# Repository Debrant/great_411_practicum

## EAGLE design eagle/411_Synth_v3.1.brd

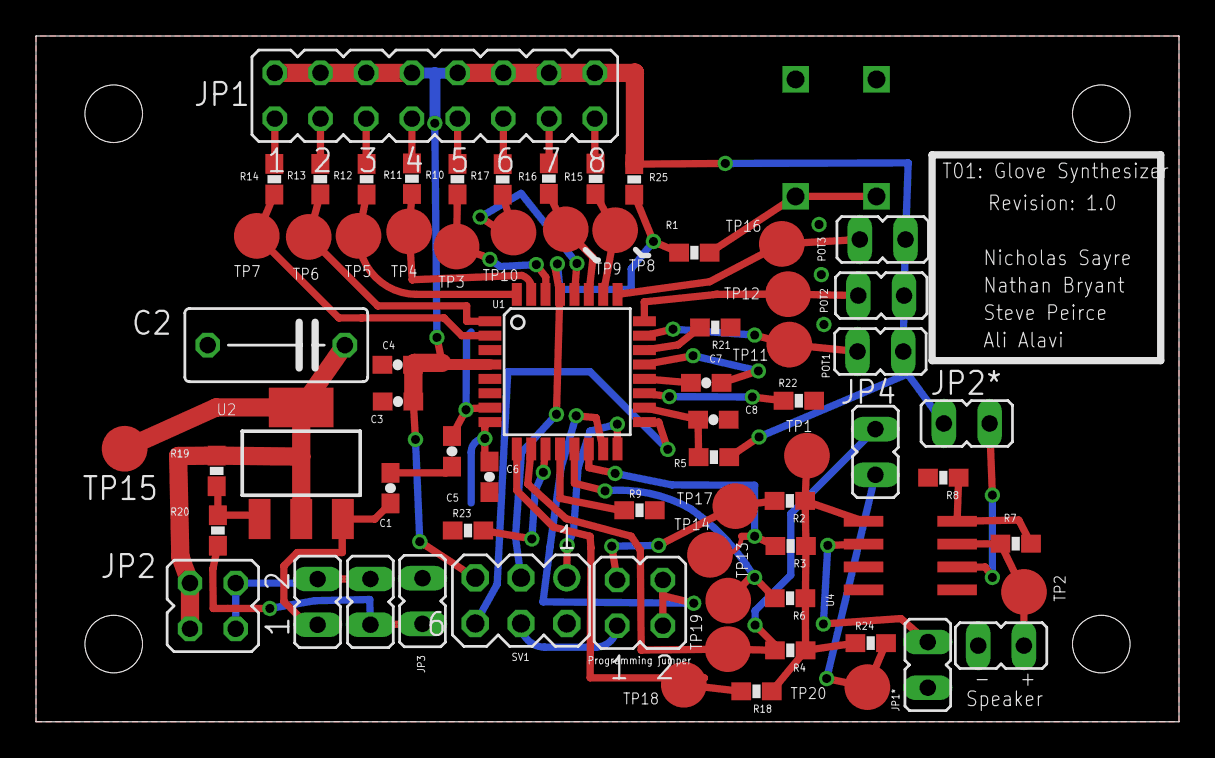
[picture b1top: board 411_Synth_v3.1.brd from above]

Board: 2 copper layers, 63.5 x 38.1 mm, 72 parts (1 on the bottom side), 50 nets.

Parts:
20MHZ: CSM-7X; CSM-7X-DU
C1: 10u; 0603-CAP
C2: 100u; C075-042X103
C3, C4, C7, C8: 100n; 0603-CAP
C5, C6: 22p; 0603-CAP
JP1: 0; JP8Q
JP1*, JP2*, JP3, JP4: 0; JP1
JP2: 0; JP2Q
POT1, POT2, POT3: 0; JP1
PROG.JMP: 0; JP2Q
R1, R20: 330; 0603-RES
R2, R3, R5, R6, R8, R18: 100k; 0603-RES
R4, R24: NP; 0603-RES
R7, R9, R10, R11, R12, R13, R14, R15, R16, R17, R21, R22, R23: 1k; 0603-RES
R19: 100; 0603-RES
R25: 10k; 0603-RES
SV1: 0; MA03-2
SW1: RESET_BUTTON
TP1, TP2, TP3, TP4, TP5, TP6, TP7, TP8, TP9, TP10, TP11, TP12, TP13, TP14, TP15, TP16, TP17, TP18, TP19, TP20: PTR1B2,54; B2,54
U1: ATMEGA328P; TQFP32-08
U2: ZLDO1117; SOT223
U4: LT1013; SO08
U$1: SPEAKER; JP1
U$7: POWER_SWITCH; JP1
U$8: 9VOLTBATTERY; JP1

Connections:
5V: C2.1, JP2.3, JP2.4, R19.2, TP15.TP, U2.2, U2.4
9V: JP2.1, JP2.2, U$7.1, U$8.1
+5V: C3.1, C4.1, JP1.2, JP1.4, JP1.6, JP1.8, JP1.10, JP1.12, JP1.14, JP1.16, JP2*.2, POT1.1, POT2.1, POT3.1, R5.2, R25.2, SV1.5, U1.4
GND: C1.2, C2.2, C3.2, C4.2, C5.2, C6.2, C7.2, C8.2, JP1*.2, JP3.1, JP3.2, R8.2, R9.1, R20.1, R21.1, R22.1, R23.1, SV1.2, SW1.1, SW1.2, U1.3, U1.5, U1.21, U4.3, U4.4, U4.5, U$1.2, U$8.2
MISO: SV1.1, U1.16
MOSI: PROG.JMP.1, SV1.4
unnamed: C7.1, U1.20
unnamed: R2.1, R3.1, R4.1, R6.1, R18.1, R24.1, TP1.TP, U4.1
unnamed: JP1.9, R10.2
unnamed: JP1.7, R11.2
unnamed: JP1.5, R12.2
unnamed: 20MHZ.1, C5.1, U1.7
unnamed: 20MHZ.2, C6.1, U1.8
unnamed: C8.1, R5.1, U1.18
unnamed: R21.2, U1.22
unnamed: R22.2, U1.19
unnamed: JP1.3, R13.2
unnamed: JP1.1, R14.2
unnamed: JP1.15, R15.2
unnamed: JP1.13, R16.2
unnamed: R7.1, R8.1, U4.8
unnamed: R9.2, U1.12
unnamed: JP4.1, R24.2, TP20.TP
unnamed: R1.2, SW1.3, SW1.4
unnamed: JP1.11, R17.2
unnamed: R7.2, TP2.TP, U4.7, U$1.1
unnamed: R19.1, R20.2, U2.1
unnamed: C1.1, U2.3, U$7.2
PB1: R6.2, TP13.TP, U1.13
PB2: R3.2, TP14.TP, U1.14
PB3: PROG.JMP.3, R2.2, TP17.TP
PB3/MOSI: PROG.JMP.2, PROG.JMP.4, U1.15
PC0: POT1.2, TP11.TP, U1.23
PC1: POT2.2, TP12.TP, U1.24
PC2: POT3.2, TP16.TP, U1.25
PC3: R15.1, TP8.TP, U1.26
PC4: R16.1, TP9.TP, U1.27
PC5: R17.1, TP10.TP, U1.28
PD0: R10.1, TP3.TP, U1.30
PD1: R11.1, TP4.TP, U1.31
PD2: R12.1, TP5.TP, U1.32
PD3: R13.1, TP6.TP, U1.1
PD4: R14.1, TP7.TP, U1.2
PD5: R18.2, TP18.TP, U1.9
PD6: JP4.2, R4.2, TP19.TP, U1.10
PD7: R23.2, U1.11
RESET: R1.1, R25.1, SV1.3, U1.29
SCK: SV1.6, U1.17
V+: JP2*.1, U4.6
V-: JP1*.1, U4.2

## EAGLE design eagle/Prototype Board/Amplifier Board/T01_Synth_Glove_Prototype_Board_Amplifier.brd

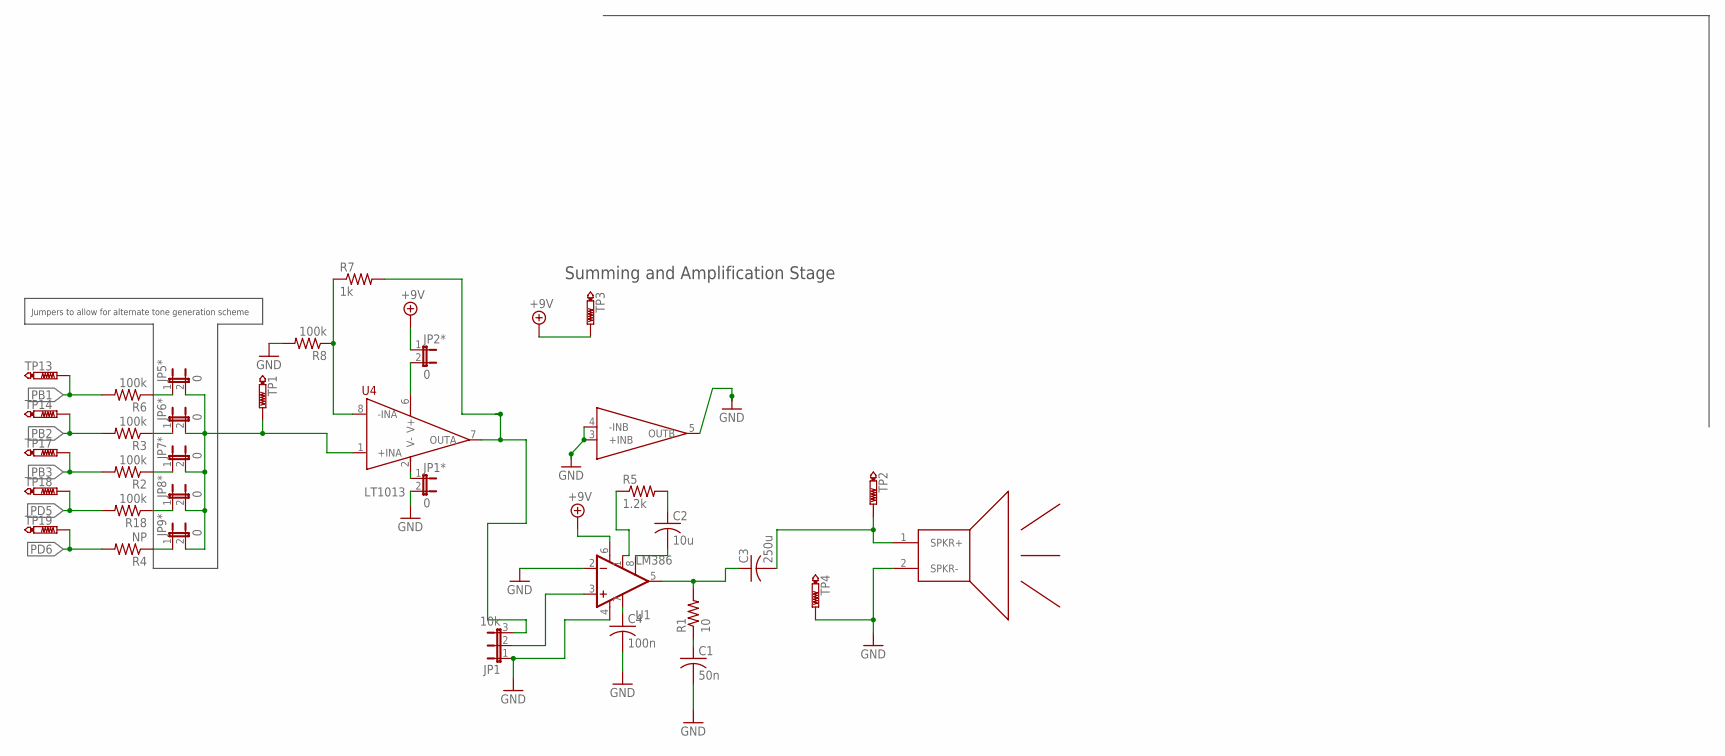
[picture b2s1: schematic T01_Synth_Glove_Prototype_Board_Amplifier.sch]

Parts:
C1: 50n; C025-030X050
C2: 10u; C025-030X050
C3: 250u; C025-030X050
C4: 100n; C025-030X050
JP1: 10k; JP2
JP1*, JP2*, JP5*, JP6*, JP7*, JP8*, JP9*: 0; JP1
R1: 10; 0204V
R2, R3, R6, R8, R18: 100k; 0603-RES
R4: NP; 0603-RES
R5: 1.2k; 0204V
R7: 1k; 0603-RES
TP1, TP2, TP3, TP4, TP13, TP14, TP17, TP18, TP19: PTR1B2,54; B2,54
U1: LM386; DIP08
U4: LT1013; SO08
U$1: SPEAKER; JP1

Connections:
+9V: JP2*.1, TP3.TP, U1.6 (V+)
GND: C1.2, C4.2, JP1.1, JP1*.2, R8.2, TP4.TP, U1.2 (-IN), U1.4 (V-), U4.3 (+INB), U4.4 (-INB), U4.5 (OUTB), U$1.2 (SPKR-)
unnamed: C3.1, R1.2, U1.5 (OUT)
unnamed: JP5*.2, JP6*.2, JP7*.2, JP8*.2, JP9*.2, TP1.TP, U4.1 (+INA)
unnamed: JP1.3, R7.2, U4.7 (OUTA)
unnamed: C1.1, R1.1
unnamed: C3.2, TP2.TP, U$1.1 (SPKR+)
unnamed: C2.2, U1.8 (GAIN)
unnamed: C2.1, R5.2
unnamed: R5.1, U1.1 (GAIN)
unnamed: C4.1, U1.7 (BP)
unnamed: JP1.2, U1.3 (+IN)
unnamed: R7.1, R8.1, U4.8 (-INA)
unnamed: JP5*.1, R6.1
unnamed: JP6*.1, R3.1
unnamed: JP7*.1, R2.1
unnamed: JP2*.2, U4.6 (V+)
unnamed: JP8*.1, R18.1
unnamed: JP9*.1, R4.1
PB1: R6.2, TP13.TP
PB2: R3.2, TP14.TP
PB3: R2.2, TP17.TP
PD5: R18.2, TP18.TP
PD6: R4.2, TP19.TP
V-: JP1*.1, U4.2 (V-)

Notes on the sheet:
Summing and Amplification Stage
Jumpers to allow for alternate tone generation scheme

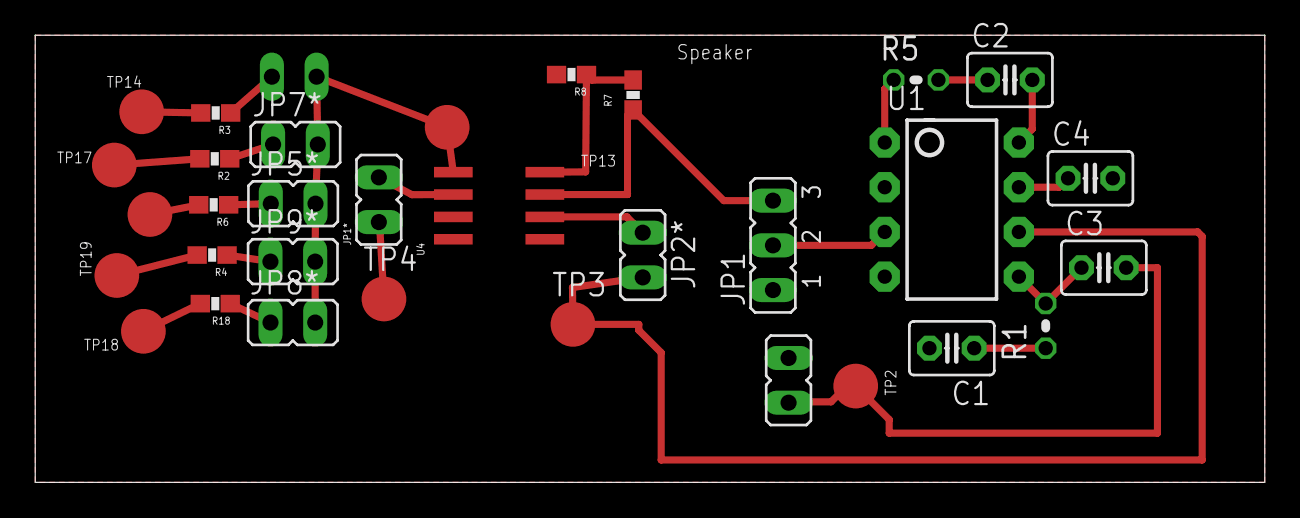
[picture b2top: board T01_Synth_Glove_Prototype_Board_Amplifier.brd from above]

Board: 2 copper layers, 69.8 x 25.4 mm, 33 parts (1 on the bottom side), 25 nets.

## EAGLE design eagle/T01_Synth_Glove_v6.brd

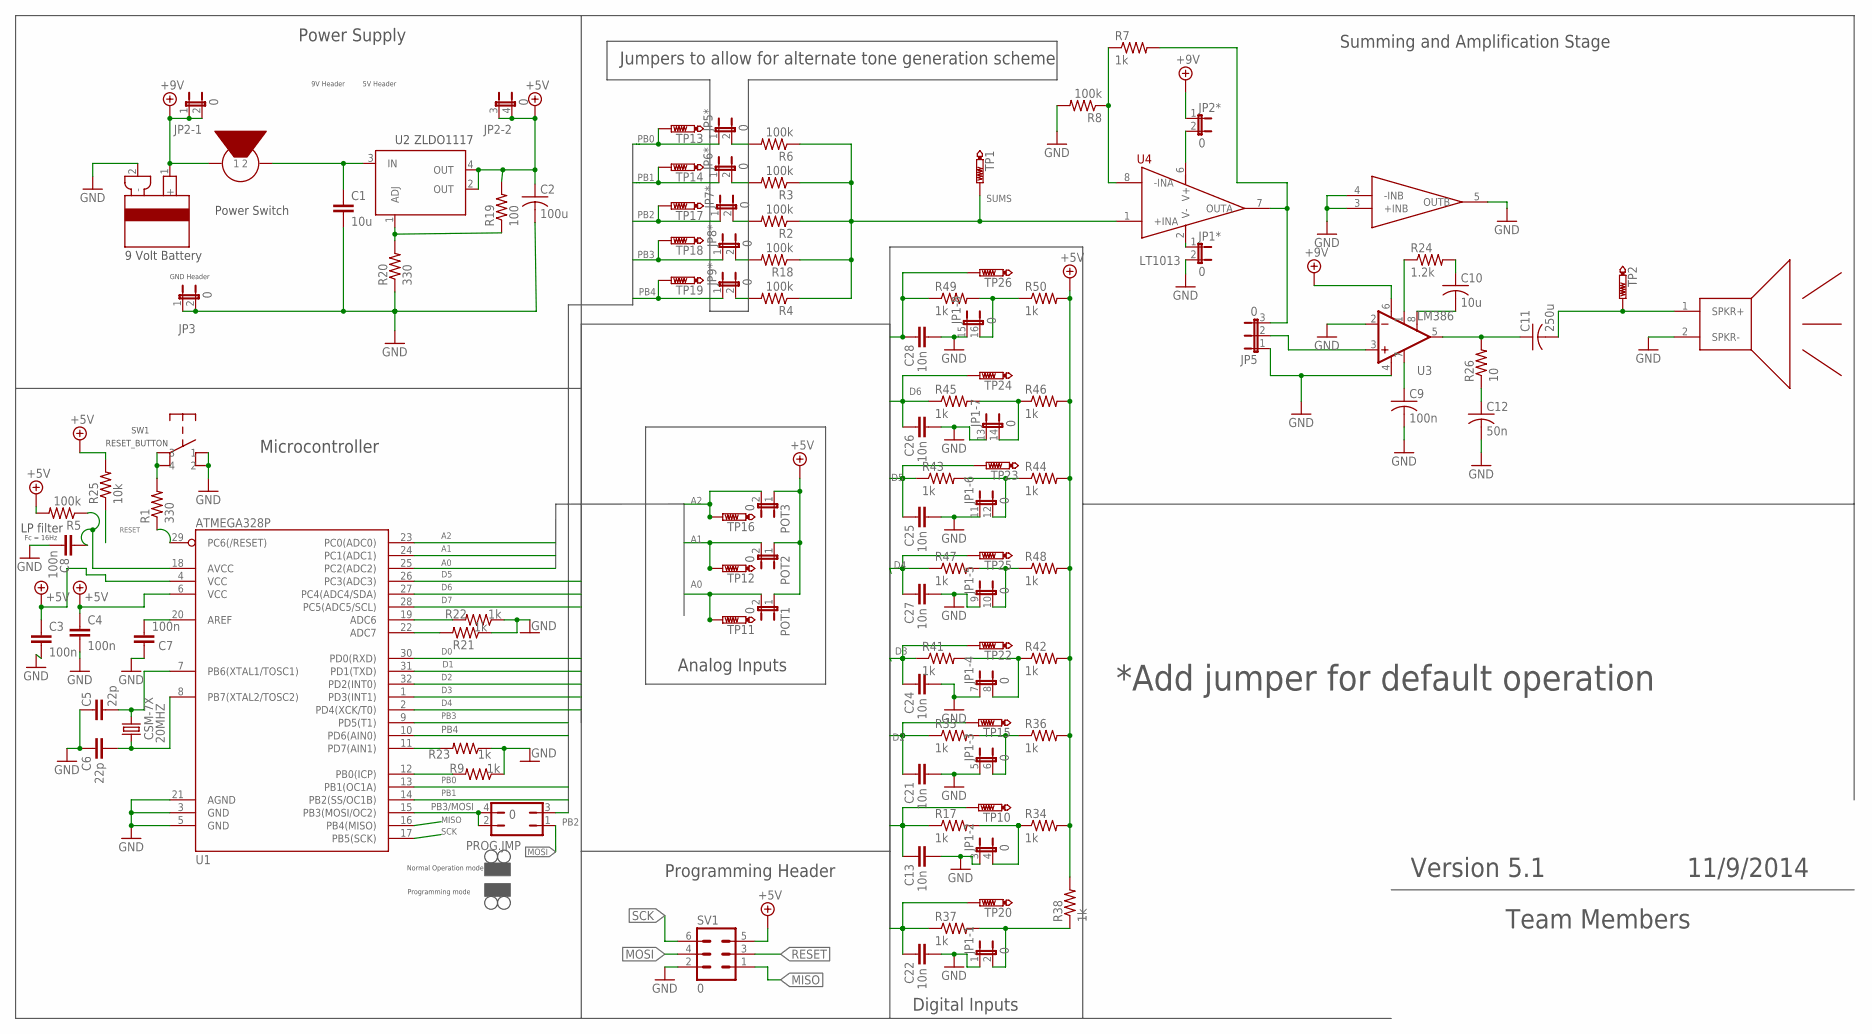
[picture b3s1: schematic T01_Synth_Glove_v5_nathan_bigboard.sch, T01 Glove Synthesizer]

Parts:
20MHZ: CSM-7X; CSM-7X-DU
C1: 10u; 0603-CAP
C2: 100u; C075-042X103
C3, C4, C7, C8: 100n; 0603-CAP
C5, C6: 22p; 0603-CAP
C9: 100n; C025-030X050
C10: 10u; C025-030X050
C11: 250u; C025-030X050
C12: 50n; C025-030X050
C13, C21, C22, C24, C25, C26, C27, C28: 10n; 0603-CAP
JP1: 0; JP8Q
JP1*, JP2*, JP3, JP5*, JP6*, JP7*, JP8*, JP9*: 0; JP1
JP2: 0; JP2Q
JP5: 0; JP2
POT1, POT2, POT3: 0; JP1
PROG.JMP: 0; JP2Q
R1, R20: 330; 0603-RES
R2, R3, R4, R5, R6, R8, R18: 100k; 0603-RES
R7, R9, R17, R21, R22, R23, R34, R35, R36, R37, R38, R41, R42, R43, R44, R45, R46, R47, R48, R49, R50: 1k; 0603-RES
R19: 100; 0603-RES
R24: 1.2k; 0204V
R25: 10k; 0603-RES
R26: 10; 0204V
SV1: 0; MA03-2
SW1: RESET_BUTTON
TP1, TP2, TP10, TP11, TP12, TP13, TP14, TP15, TP16, TP17, TP18, TP19, TP20, TP22, TP23, TP24, TP25, TP26: PTR1B2,54; B2,54
U1: ATMEGA328P; TQFP32-08
U2: ZLDO1117; SOT223
U3: LM386; DIP08
U4: LT1013; SO08
U$1: SPEAKER; JP1
U$7: POWER_SWITCH; JP1
U$8: 9VOLTBATTERY; JP1

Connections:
+5V: C2.1, C3.1, C4.1, JP2.3 (1), JP2.4 (2), POT1.1, POT2.1, POT3.1, R5.2, R19.2, R25.2, R34.2, R36.2, R38.2, R42.2, R44.2, R46.2, R48.2, R50.2, SV1.5, U1.4 (VCC), U1.6 (VCC), U2.2 (OUT), U2.4 (OUT); also elsewhere on the board
+9V: JP2.1, JP2.2, JP2*.1, U3.6 (V+), U$7.1, U$8.1 (+); also elsewhere on the board
A0: POT1.2, TP11.TP, U1.25 (PC2(ADC2))
A1: POT2.2, TP12.TP, U1.24 (PC1(ADC1))
A2: POT3.2, TP16.TP, U1.23 (PC0(ADC0))
D0: C22.2, R37.1, TP20.TP, U1.30 (PD0(RXD))
D1: C13.2, R17.1, TP10.TP, U1.31 (PD1(TXD))
D2: C21.2, R35.1, TP15.TP, U1.32 (PD2(INT0))
D3: C24.2, R41.1, TP22.TP, U1.1 (PD3(INT1))
D4: C27.2, R47.1, TP25.TP, U1.2 (PD4(XCK/T0))
D5: C25.2, R43.1, TP23.TP, U1.26 (PC3(ADC3))
D6: C26.2, R45.1, TP24.TP, U1.27 (PC4(ADC4/SDA))
D7: C28.2, R49.1, TP26.TP, U1.28 (PC5(ADC5/SCL))
MISO: SV1.1, U1.16 (PB4(MISO))
MOSI: PROG.JMP.1, SV1.4
unnamed: C7.1, U1.20 (AREF)
unnamed: 20MHZ.1, C5.1, U1.7 (PB6(XTAL1/TOSC1))
unnamed: 20MHZ.2, C6.1, U1.8 (PB7(XTAL2/TOSC2))
unnamed: C8.1, R5.1, U1.18 (AVCC)
unnamed: R21.2, U1.22 (ADC7)
unnamed: R22.2, U1.19 (ADC6)
unnamed: JP1.6 (2), R35.2, R36.1
unnamed: R7.1, R8.1, U4.8 (-INA)
unnamed: R9.2, U1.12 (PB0(ICP))
unnamed: JP5*.2, R6.2
unnamed: JP9*.2, R4.2
unnamed: R1.2, SW1.3, SW1.4
unnamed: JP8*.2, R18.2
unnamed: C11.2, TP2.TP, U$1.1 (SPKR+)
unnamed: JP7*.2, R2.2
unnamed: JP2*.2, U4.6 (V+)
unnamed: R19.1, R20.2, U2.1 (ADJ)
unnamed: C1.1, U2.3 (IN), U$7.2
unnamed: JP6*.2, R3.2
unnamed: C10.2, U3.8 (GAIN)
unnamed: JP1.2, R37.2, R38.1
unnamed: C11.1, R26.2, U3.5 (OUT)
unnamed: C12.1, R26.1
unnamed: JP1.16 (2), R49.2, R50.1
PB0: JP5*.1, TP13.TP, U1.13 (PB1(OC1A))
PB1: JP6*.1, TP14.TP, U1.14 (PB2(SS/OC1B))
PB2: JP7*.1, PROG.JMP.3, TP17.TP
PB3: JP8*.1, TP18.TP, U1.9 (PD5(T1))
PB3/MOSI: PROG.JMP.2, PROG.JMP.4, U1.15 (PB3(MOSI/OC2))
PB4: JP9*.1, TP19.TP, U1.10 (PD6(AIN0))
PD7: R23.2, U1.11 (PD7(AIN1))
SCK: SV1.6, U1.17 (PB5(SCK))
SUMS: R2.1, R3.1, R4.1, R6.1, R18.1, TP1.TP, U4.1 (+INA)
V-: JP1*.1, U4.2 (V-)

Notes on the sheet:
Power Switch
Programming Header
Digital Inputs
Power Supply
Microcontroller
Summing and Amplification Stage
Analog Inputs
LP filter
*Add jumper for default operation
5V Header
9V Header
GND Header
Fc = 16Hz
Jumpers to allow for alternate tone generation scheme
Programming mode
Normal Operation mode
Team Members
Version 5.1
11/9/2014

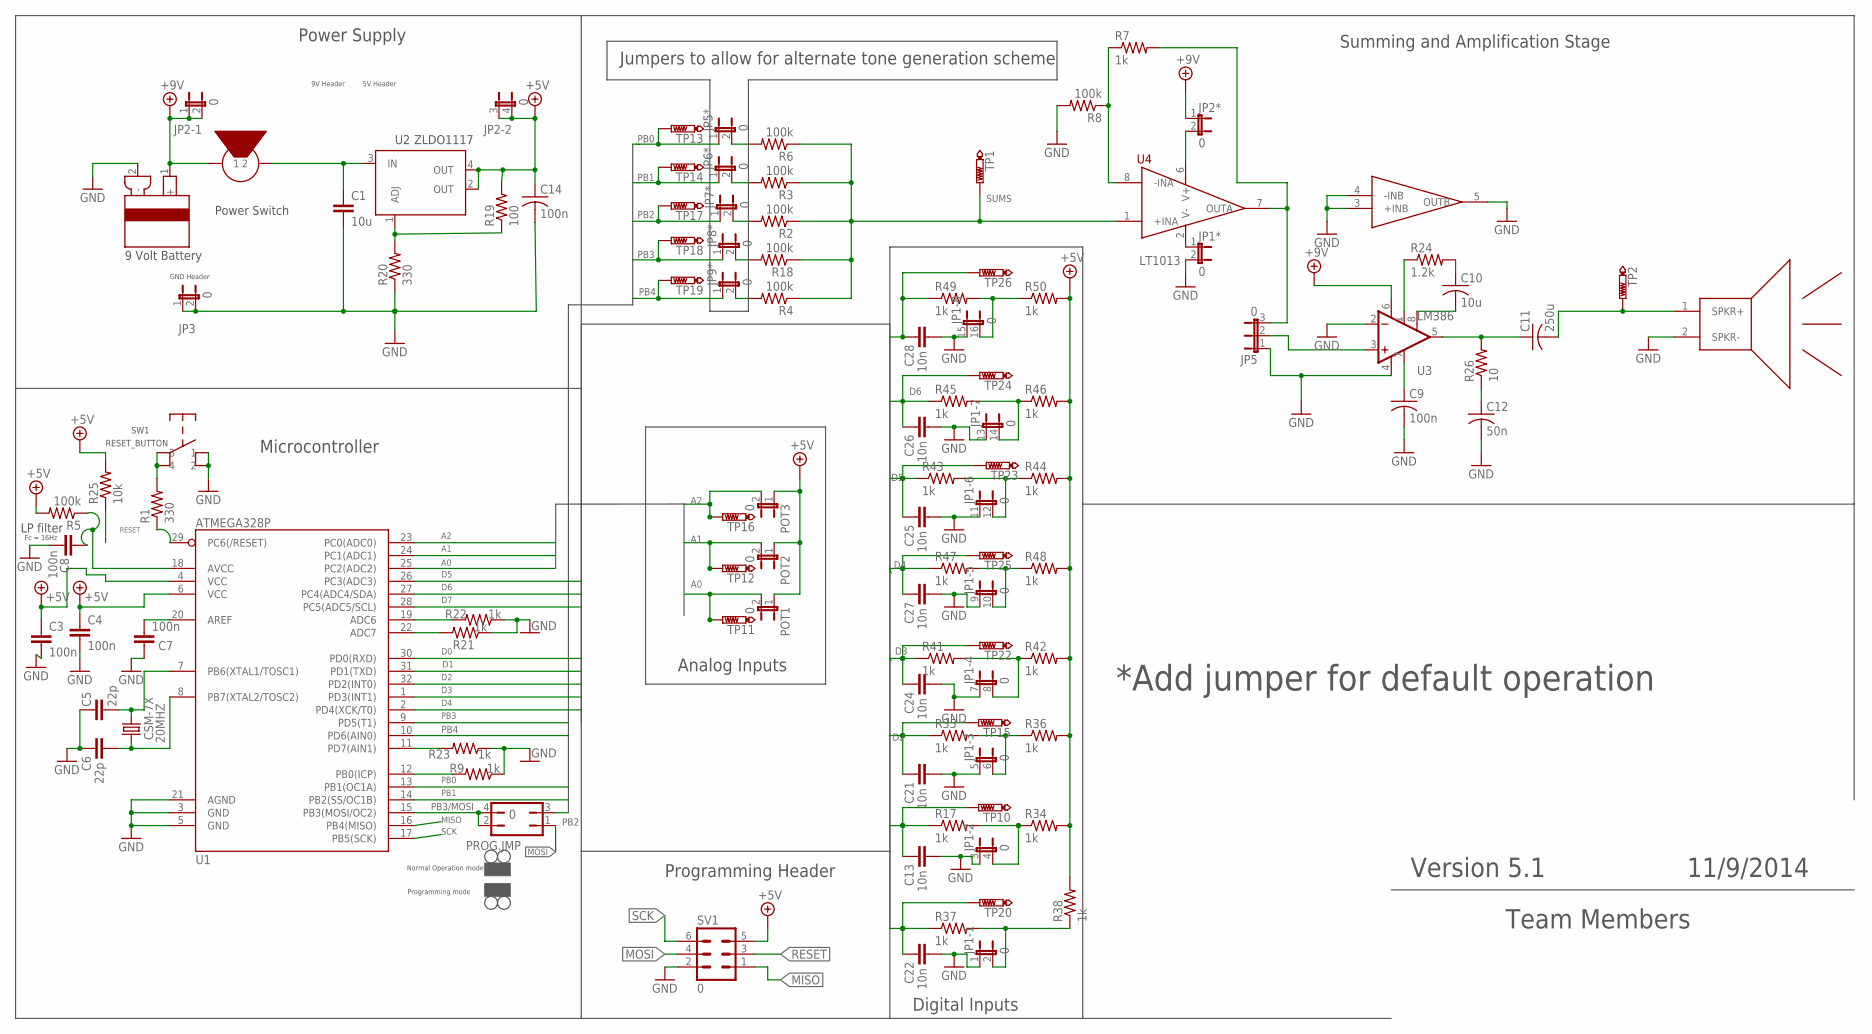
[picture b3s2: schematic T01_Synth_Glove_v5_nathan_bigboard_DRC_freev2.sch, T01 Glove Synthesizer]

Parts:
20MHZ: CSM-7X; CSM-7X-DU
C1: 10u; 0603-CAP
C3, C4, C7, C8: 100n; 0603-CAP
C5, C6: 22p; 0603-CAP
C9, C14: 100n; C025-030X050
C10: 10u; C025-030X050
C11: 250u; C025-030X050
C12: 50n; C025-030X050
C13, C21, C22, C24, C25, C26, C27, C28: 10n; 0603-CAP
JP1: 0; JP8Q
JP1*, JP2*, JP3, JP5*, JP6*, JP7*, JP8*, JP9*: 0; JP1
JP2: 0; JP2Q
JP5: 0; JP2
POT1, POT2, POT3: 0; JP1
PROG.JMP: 0; JP2Q
R1, R20: 330; 0603-RES
R2, R3, R4, R5, R6, R8, R18: 100k; 0603-RES
R7, R9, R17, R21, R22, R23, R34, R35, R36, R37, R38, R41, R42, R43, R44, R45, R46, R47, R48, R49, R50: 1k; 0603-RES
R19: 100; 0603-RES
R24: 1.2k; 0204V
R25: 10k; 0603-RES
R26: 10; 0204V
SV1: 0; MA03-2
SW1: RESET_BUTTON
TP1, TP2, TP10, TP11, TP12, TP13, TP14, TP15, TP16, TP17, TP18, TP19, TP20, TP22, TP23, TP24, TP25, TP26: PTR1B2,54; B2,54
U1: ATMEGA328P; TQFP32-08
U2: ZLDO1117; SOT223
U3: LM386; DIP08
U4: LT1013; SO08
U$1: SPEAKER; JP1
U$7: POWER_SWITCH; JP1
U$8: 9VOLTBATTERY; JP1

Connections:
+5V: C3.1, C4.1, C14.1, JP2.3 (1), JP2.4 (2), POT1.1, POT2.1, POT3.1, R5.2, R19.2, R25.2, R34.2, R36.2, R38.2, R42.2, R44.2, R46.2, R48.2, R50.2, SV1.5, U1.4 (VCC), U1.6 (VCC), U2.2 (OUT), U2.4 (OUT); also elsewhere on the board
+9V: C14.2, JP2.1, JP2.2, JP2*.1, U3.6 (V+), U$7.1, U$8.1 (+)
A0: POT1.2, TP11.TP, U1.25 (PC2(ADC2))
A1: POT2.2, TP12.TP, U1.24 (PC1(ADC1))
A2: POT3.2, TP16.TP, U1.23 (PC0(ADC0))
D0: C22.2, R37.1, TP20.TP, U1.30 (PD0(RXD))
D1: C13.2, R17.1, TP10.TP, U1.31 (PD1(TXD))
D2: C21.2, R35.1, TP15.TP, U1.32 (PD2(INT0))
D3: C24.2, R41.1, TP22.TP, U1.1 (PD3(INT1))
D4: C27.2, R47.1, TP25.TP, U1.2 (PD4(XCK/T0))
D5: C25.2, R43.1, TP23.TP, U1.26 (PC3(ADC3))
D6: C26.2, R45.1, TP24.TP, U1.27 (PC4(ADC4/SDA))
D7: C28.2, R49.1, TP26.TP, U1.28 (PC5(ADC5/SCL))
MISO: SV1.1, U1.16 (PB4(MISO))
MOSI: PROG.JMP.1, SV1.4
unnamed: C7.1, U1.20 (AREF)
unnamed: 20MHZ.1, C5.1, U1.7 (PB6(XTAL1/TOSC1))
unnamed: 20MHZ.2, C6.1, U1.8 (PB7(XTAL2/TOSC2))
unnamed: C8.1, R5.1, U1.18 (AVCC)
unnamed: R21.2, U1.22 (ADC7)
unnamed: R22.2, U1.19 (ADC6)
unnamed: JP1.6 (2), R35.2, R36.1
unnamed: R7.1, R8.1, U4.8 (-INA)
unnamed: R9.2, U1.12 (PB0(ICP))
unnamed: JP5*.2, R6.2
unnamed: JP9*.2, R4.2
unnamed: R1.2, SW1.3, SW1.4
unnamed: JP8*.2, R18.2
unnamed: C11.2, TP2.TP, U$1.1 (SPKR+)
unnamed: JP7*.2, R2.2
unnamed: JP2*.2, U4.6 (V+)
unnamed: R19.1, R20.2, U2.1 (ADJ)
unnamed: C1.1, U2.3 (IN), U$7.2
unnamed: JP6*.2, R3.2
unnamed: C10.2, U3.8 (GAIN)
unnamed: JP1.2, R37.2, R38.1
unnamed: C11.1, R26.2, U3.5 (OUT)
unnamed: C12.1, R26.1
unnamed: JP1.16 (2), R49.2, R50.1
PB0: JP5*.1, TP13.TP, U1.13 (PB1(OC1A))
PB1: JP6*.1, TP14.TP, U1.14 (PB2(SS/OC1B))
PB2: JP7*.1, PROG.JMP.3, TP17.TP
PB3: JP8*.1, TP18.TP, U1.9 (PD5(T1))
PB3/MOSI: PROG.JMP.2, PROG.JMP.4, U1.15 (PB3(MOSI/OC2))
PB4: JP9*.1, TP19.TP, U1.10 (PD6(AIN0))
PD7: R23.2, U1.11 (PD7(AIN1))
SCK: SV1.6, U1.17 (PB5(SCK))
SUMS: R2.1, R3.1, R4.1, R6.1, R18.1, TP1.TP, U4.1 (+INA)
V-: JP1*.1, U4.2 (V-)

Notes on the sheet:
Power Switch
Programming Header
Digital Inputs
Power Supply
Microcontroller
Summing and Amplification Stage
Analog Inputs
LP filter
*Add jumper for default operation
5V Header
9V Header
GND Header
Fc = 16Hz
Jumpers to allow for alternate tone generation scheme
Programming mode
Normal Operation mode
Team Members
Version 5.1
11/9/2014

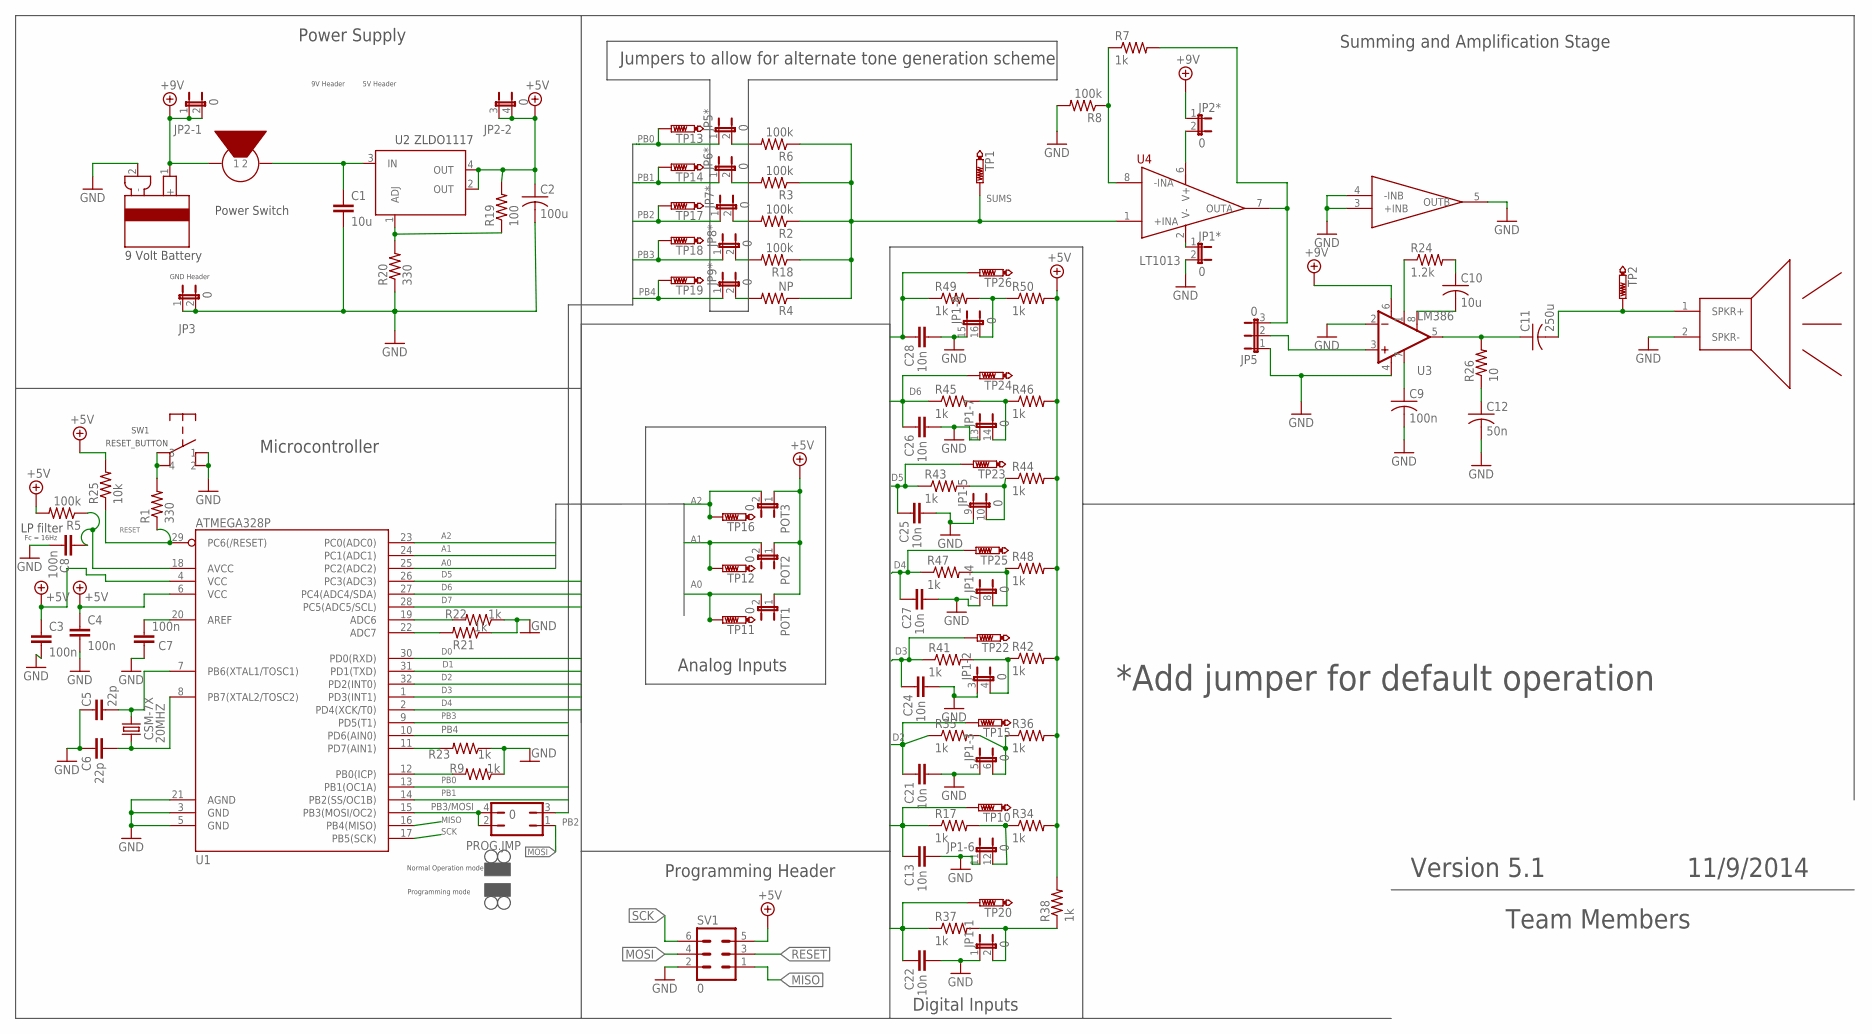
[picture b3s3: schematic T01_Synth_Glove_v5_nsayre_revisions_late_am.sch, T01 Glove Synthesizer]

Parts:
20MHZ: CSM-7X; CSM-7X-DU
C1: 10u; 0603-CAP
C2: 100u; C025-030X050
C3, C4, C7, C8: 100n; 0603-CAP
C5, C6: 22p; 0603-CAP
C9: 100n; C025-030X050
C10: 10u; C025-030X050
C11: 250u; C025-030X050
C12: 50n; C025-030X050
C13, C21, C22, C24, C25, C26, C27, C28: 10n; 0603-CAP
JP1: 0; JP8Q
JP1*, JP2*, JP3, JP5*, JP6*, JP7*, JP8*, JP9*: 0; JP1
JP2: 0; JP2Q
JP5: 0; JP2
POT1, POT2, POT3: 0; JP1
PROG.JMP: 0; JP2Q
R1, R20: 330; 0603-RES
R2, R3, R5, R6, R8, R18: 100k; 0603-RES
R4: NP; 0603-RES
R7, R9, R17, R21, R22, R23, R34, R35, R36, R37, R38, R41, R42, R43, R44, R45, R46, R47, R48, R49, R50: 1k; 0603-RES
R19: 100; 0603-RES
R24: 1.2k; 0204V
R25: 10k; 0603-RES
R26: 10; 0204V
SV1: 0; MA03-2
SW1: RESET_BUTTON
TP1, TP2, TP10, TP11, TP12, TP13, TP14, TP15, TP16, TP17, TP18, TP19, TP20, TP22, TP23, TP24, TP25, TP26: PTR1B2,54; B2,54
U1: ATMEGA328P; TQFP32-08
U2: ZLDO1117; SOT223
U3: LM386; DIP08
U4: LT1013; SO08
U$1: SPEAKER; JP1
U$7: POWER_SWITCH; JP1
U$8: 9VOLTBATTERY; JP1

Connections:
+5V: C2.1, C3.1, C4.1, JP2.3 (1), JP2.4 (2), POT1.1, POT2.1, POT3.1, R5.2, R19.2, R25.2, R34.2, R36.2, R38.2, R42.2, R44.2, R46.2, R48.2, R50.2, SV1.5, U1.4 (VCC), U1.6 (VCC), U2.2 (OUT), U2.4 (OUT); also elsewhere on the board
+9V: JP2.1, JP2.2, JP2*.1, U3.6 (V+), U$7.1, U$8.1 (+); also elsewhere on the board
A0: POT1.2, TP11.TP, U1.25 (PC2(ADC2))
A1: POT2.2, TP12.TP, U1.24 (PC1(ADC1))
A2: POT3.2, TP16.TP, U1.23 (PC0(ADC0))
D0: C22.2, R37.1, TP20.TP, U1.30 (PD0(RXD))
D1: C13.2, R17.1, TP10.TP, U1.31 (PD1(TXD))
D2: C21.2, R35.1, TP15.TP, U1.32 (PD2(INT0))
D3: C24.2, R41.1, TP22.TP, U1.1 (PD3(INT1))
D4: C27.2, R47.1, TP25.TP, U1.2 (PD4(XCK/T0))
D5: C25.2, R43.1, TP23.TP, U1.26 (PC3(ADC3))
D6: C26.2, R45.1, TP24.TP, U1.27 (PC4(ADC4/SDA))
D7: C28.2, R49.1, TP26.TP, U1.28 (PC5(ADC5/SCL))
MISO: SV1.1, U1.16 (PB4(MISO))
MOSI: PROG.JMP.1, SV1.4
unnamed: C7.1, U1.20 (AREF)
unnamed: 20MHZ.1, C5.1, U1.7 (PB6(XTAL1/TOSC1))
unnamed: 20MHZ.2, C6.1, U1.8 (PB7(XTAL2/TOSC2))
unnamed: C8.1, R5.1, U1.18 (AVCC)
unnamed: R21.2, U1.22 (ADC7)
unnamed: R22.2, U1.19 (ADC6)
unnamed: JP1.6 (2), R35.2, R36.1
unnamed: R7.1, R8.1, U4.8 (-INA)
unnamed: R9.2, U1.12 (PB0(ICP))
unnamed: JP5*.2, R6.2
unnamed: JP9*.2, R4.2
unnamed: R1.2, SW1.3, SW1.4
unnamed: JP8*.2, R18.2
unnamed: C11.2, TP2.TP, U$1.1 (SPKR+)
unnamed: JP7*.2, R2.2
unnamed: JP2*.2, U4.6 (V+)
unnamed: R19.1, R20.2, U2.1 (ADJ)
unnamed: C1.1, U2.3 (IN), U$7.2
unnamed: JP6*.2, R3.2
unnamed: C10.2, U3.8 (GAIN)
unnamed: JP1.2, R37.2, R38.1
unnamed: C11.1, R26.2, U3.5 (OUT)
unnamed: C12.1, R26.1
unnamed: JP1.16 (2), R49.2, R50.1
PB0: JP5*.1, TP13.TP, U1.13 (PB1(OC1A))
PB1: JP6*.1, TP14.TP, U1.14 (PB2(SS/OC1B))
PB2: JP7*.1, PROG.JMP.3, TP17.TP
PB3: JP8*.1, TP18.TP, U1.9 (PD5(T1))
PB3/MOSI: PROG.JMP.2, PROG.JMP.4, U1.15 (PB3(MOSI/OC2))
PB4: JP9*.1, TP19.TP, U1.10 (PD6(AIN0))
PD7: R23.2, U1.11 (PD7(AIN1))
SCK: SV1.6, U1.17 (PB5(SCK))
SUMS: R2.1, R3.1, R4.1, R6.1, R18.1, TP1.TP, U4.1 (+INA)
V-: JP1*.1, U4.2 (V-)

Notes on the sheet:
Power Switch
Programming Header
Digital Inputs
Power Supply
Microcontroller
Summing and Amplification Stage
Analog Inputs
LP filter
*Add jumper for default operation
5V Header
9V Header
GND Header
Fc = 16Hz
Jumpers to allow for alternate tone generation scheme
Programming mode
Normal Operation mode
Team Members
Version 5.1
11/9/2014

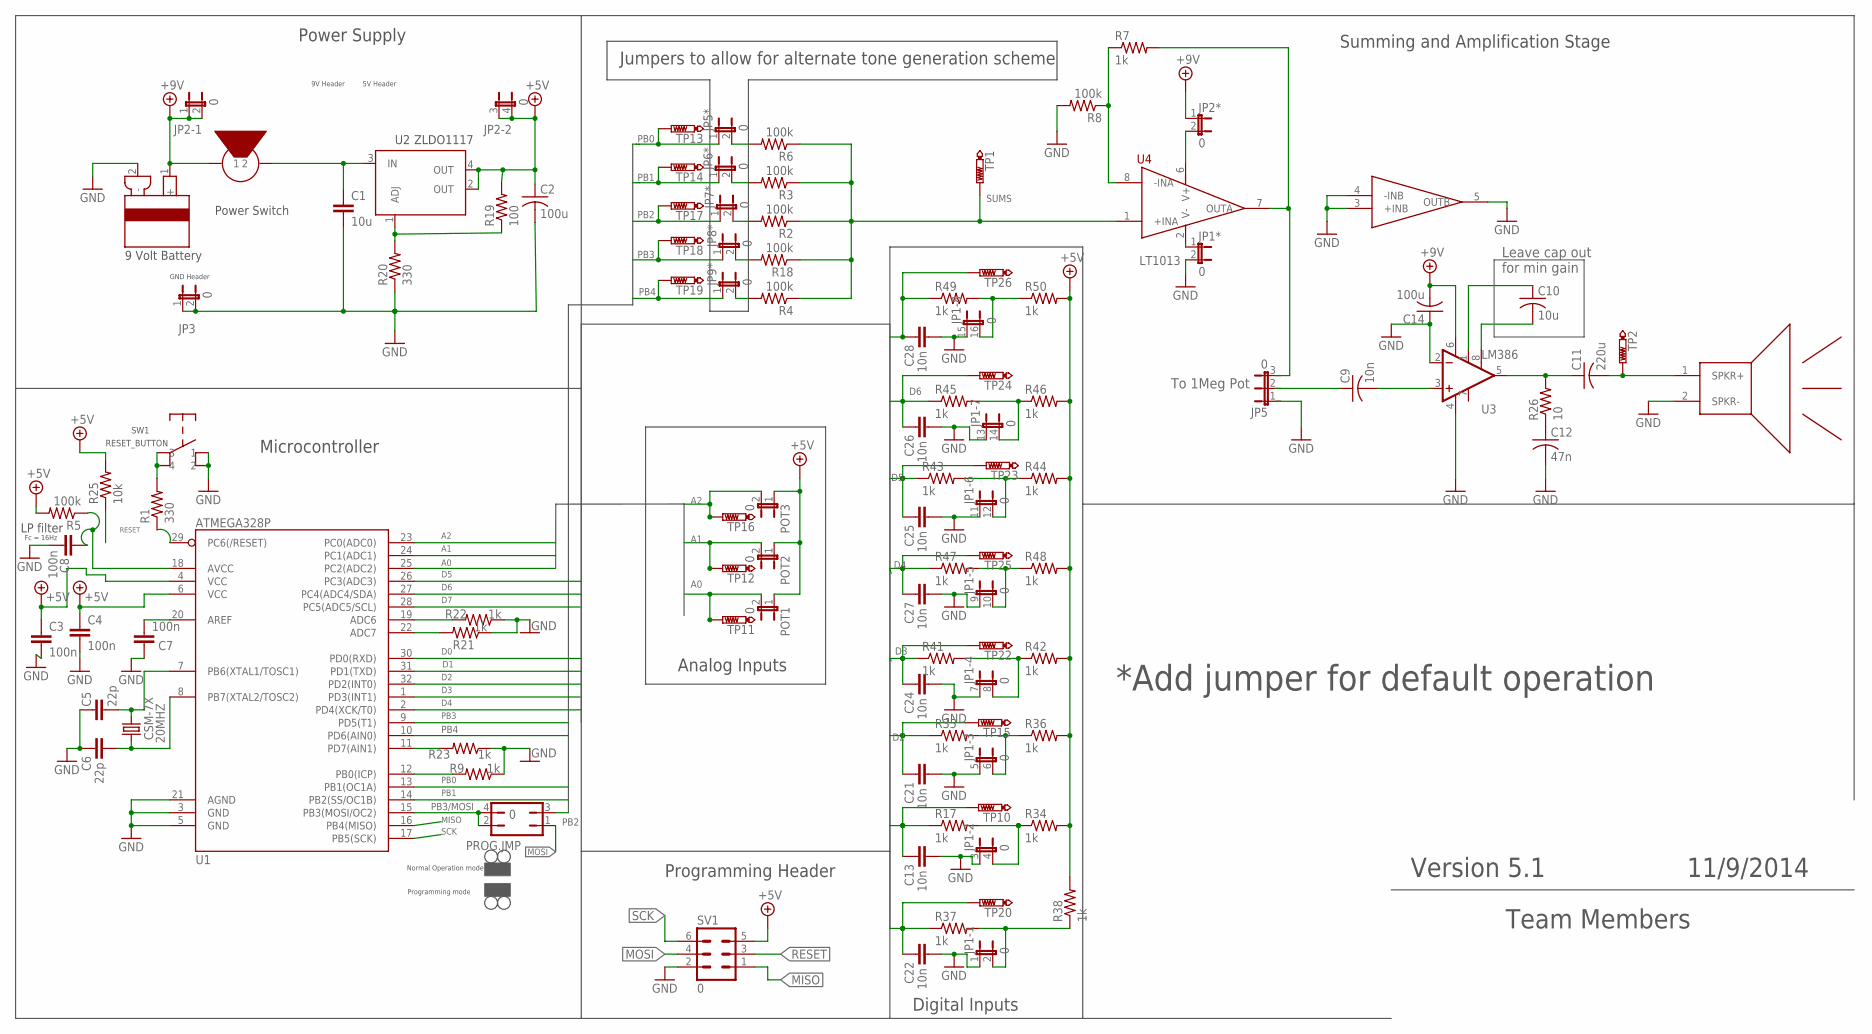
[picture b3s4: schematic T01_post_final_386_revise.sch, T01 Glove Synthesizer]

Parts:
20MHZ: CSM-7X; CSM-7X-DU
C1: 10u; 0603-CAP
C2: 100u; C075-042X103
C3, C4, C7, C8: 100n; 0603-CAP
C5, C6: 22p; 0603-CAP
C9: 10n; C025-030X050
C10: 10u; C025-030X050
C11: 220u; C025-030X050
C12: 47n; C025-030X050
C13, C21, C22, C24, C25, C26, C27, C28: 10n; 0603-CAP
C14: 100u; C025-030X050
JP1: 0; JP8Q
JP1*, JP2*, JP3, JP5*, JP6*, JP7*, JP8*, JP9*: 0; JP1
JP2: 0; JP2Q
JP5: 0; JP2
POT1, POT2, POT3: 0; JP1
PROG.JMP: 0; JP2Q
R1, R20: 330; 0603-RES
R2, R3, R4, R5, R6, R8, R18: 100k; 0603-RES
R7, R9, R17, R21, R22, R23, R34, R35, R36, R37, R38, R41, R42, R43, R44, R45, R46, R47, R48, R49, R50: 1k; 0603-RES
R19: 100; 0603-RES
R25: 10k; 0603-RES
R26: 10; 0204V
SV1: 0; MA03-2
SW1: RESET_BUTTON
TP1, TP2, TP10, TP11, TP12, TP13, TP14, TP15, TP16, TP17, TP18, TP19, TP20, TP22, TP23, TP24, TP25, TP26: PTR1B2,54; B2,54
U1: ATMEGA328P; TQFP32-08
U2: ZLDO1117; SOT223
U3: LM386; DIP08
U4: LT1013; SO08
U$1: SPEAKER; JP1
U$7: POWER_SWITCH; JP1
U$8: 9VOLTBATTERY; JP1

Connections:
+5V: C2.1, C3.1, C4.1, C14.1, JP2.3 (1), JP2.4 (2), POT1.1, POT2.1, POT3.1, R5.2, R19.2, R25.2, R34.2, R36.2, R38.2, R42.2, R44.2, R46.2, R48.2, R50.2, SV1.5, U1.4 (VCC), U1.6 (VCC), U2.2 (OUT), U2.4 (OUT)
+9V: C14.2, JP2.1, JP2.2, JP2*.1, U3.6 (V+), U$7.1, U$8.1 (+)
A0: POT1.2, TP11.TP, U1.25 (PC2(ADC2))
A1: POT2.2, TP12.TP, U1.24 (PC1(ADC1))
A2: POT3.2, TP16.TP, U1.23 (PC0(ADC0))
D0: C22.2, R37.1, TP20.TP, U1.30 (PD0(RXD))
D1: C13.2, R17.1, TP10.TP, U1.31 (PD1(TXD))
D2: C21.2, R35.1, TP15.TP, U1.32 (PD2(INT0))
D3: C24.2, R41.1, TP22.TP, U1.1 (PD3(INT1))
D4: C27.2, R47.1, TP25.TP, U1.2 (PD4(XCK/T0))
D5: C25.2, R43.1, TP23.TP, U1.26 (PC3(ADC3))
D6: C26.2, R45.1, TP24.TP, U1.27 (PC4(ADC4/SDA))
D7: C28.2, R49.1, TP26.TP, U1.28 (PC5(ADC5/SCL))
MISO: SV1.1, U1.16 (PB4(MISO))
MOSI: PROG.JMP.1, SV1.4
unnamed: C7.1, U1.20 (AREF)
unnamed: 20MHZ.1, C5.1, U1.7 (PB6(XTAL1/TOSC1))
unnamed: 20MHZ.2, C6.1, U1.8 (PB7(XTAL2/TOSC2))
unnamed: C8.1, R5.1, U1.18 (AVCC)
unnamed: R21.2, U1.22 (ADC7)
unnamed: R22.2, U1.19 (ADC6)
unnamed: JP1.6 (2), R35.2, R36.1
unnamed: R7.1, R8.1, U4.8 (-INA)
unnamed: R9.2, U1.12 (PB0(ICP))
unnamed: JP5*.2, R6.2
unnamed: JP9*.2, R4.2
unnamed: R1.2, SW1.3, SW1.4
unnamed: JP8*.2, R18.2
unnamed: C11.2, TP2.TP, U$1.1 (SPKR+)
unnamed: JP7*.2, R2.2
unnamed: JP2*.2, U4.6 (V+)
unnamed: R19.1, R20.2, U2.1 (ADJ)
unnamed: C1.1, U2.3 (IN), U$7.2
unnamed: JP6*.2, R3.2
unnamed: C10.2, U3.8 (GAIN)
unnamed: JP1.2, R37.2, R38.1
unnamed: C11.1, R26.2, U3.5 (OUT)
unnamed: C12.1, R26.1
unnamed: JP1.16 (2), R49.2, R50.1
PB0: JP5*.1, TP13.TP, U1.13 (PB1(OC1A))
PB1: JP6*.1, TP14.TP, U1.14 (PB2(SS/OC1B))
PB2: JP7*.1, PROG.JMP.3, TP17.TP
PB3: JP8*.1, TP18.TP, U1.9 (PD5(T1))
PB3/MOSI: PROG.JMP.2, PROG.JMP.4, U1.15 (PB3(MOSI/OC2))
PB4: JP9*.1, TP19.TP, U1.10 (PD6(AIN0))
PD7: R23.2, U1.11 (PD7(AIN1))
SCK: SV1.6, U1.17 (PB5(SCK))
SUMS: R2.1, R3.1, R4.1, R6.1, R18.1, TP1.TP, U4.1 (+INA)
V-: JP1*.1, U4.2 (V-)

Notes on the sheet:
Power Switch
Programming Header
Digital Inputs
Power Supply
Microcontroller
Summing and Amplification Stage
Analog Inputs
LP filter
*Add jumper for default operation
5V Header
9V Header
GND Header
Fc = 16Hz
Jumpers to allow for alternate tone generation scheme
Programming mode
Normal Operation mode
Team Members
Version 5.1
11/9/2014
To 1Meg Pot
Leave cap out for min gain

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
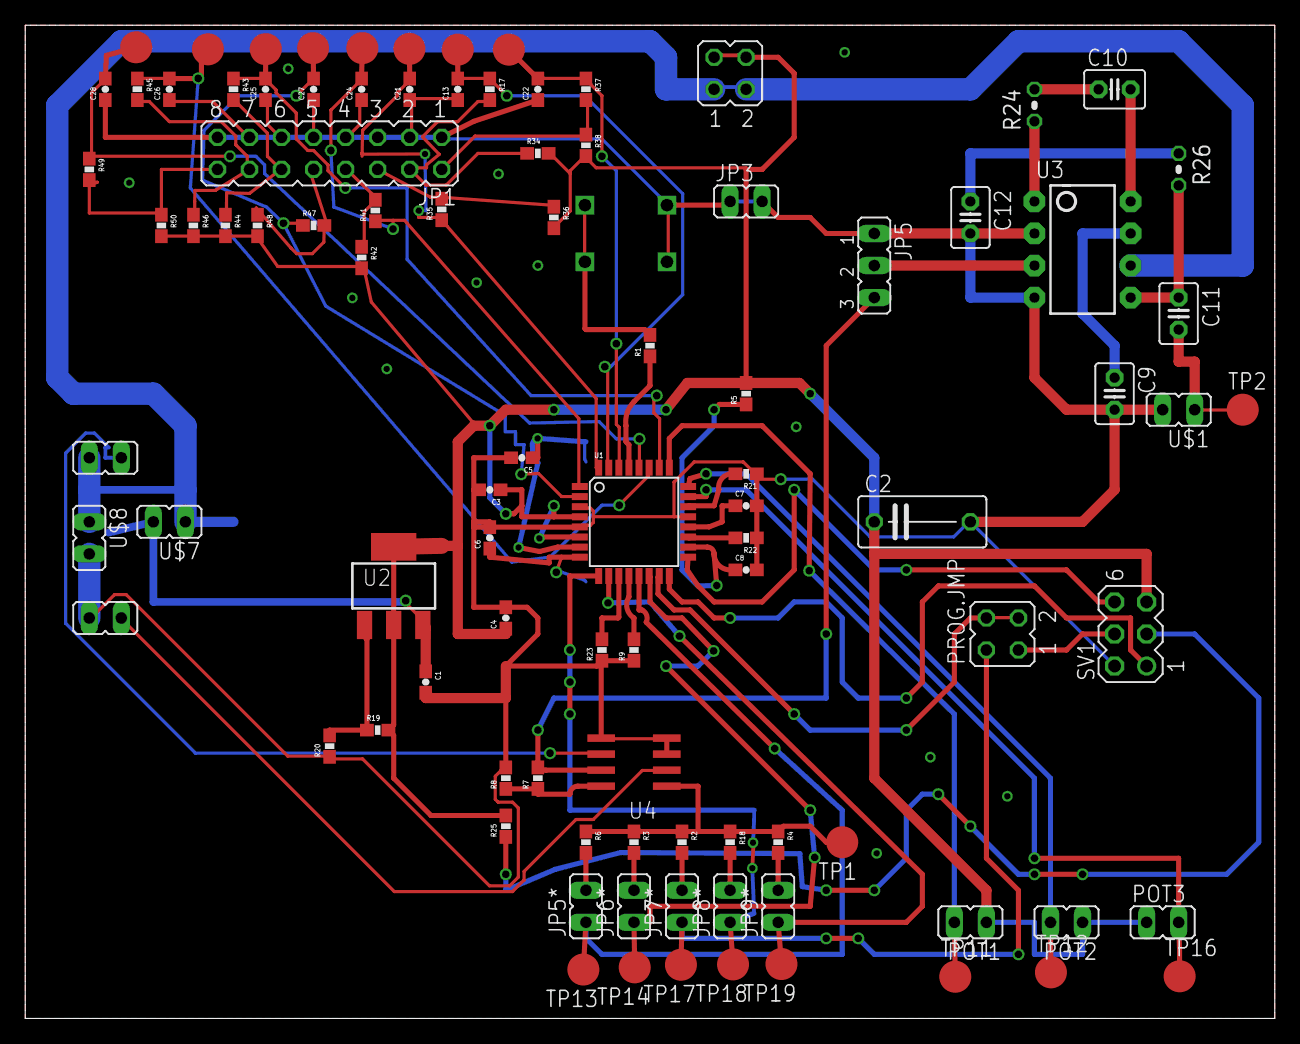
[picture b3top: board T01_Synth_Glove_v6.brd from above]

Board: 2 copper layers, 99.1 x 78.7 mm, 97 parts (1 on the bottom side), 62 nets.

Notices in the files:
parts and their libraries:
SparkFun-Capacitors: Licensing: Creative Commons ShareAlike 4.0 International - https://creativecommons.org/licenses/by-sa/4.0
